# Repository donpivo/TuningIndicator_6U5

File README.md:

# TuningIndicator_6U5
Project description: https://retronics.no/2024/08/29/diy-digital-6u5-magic-eye-replacement/
All PCB design files (KiCAD), fabrication files (gerber), 3D models (.stl) and code (C++, PlatformIO) are shared for personal use only; not for commercial use / sale of neither the complete solution nor parts of it.

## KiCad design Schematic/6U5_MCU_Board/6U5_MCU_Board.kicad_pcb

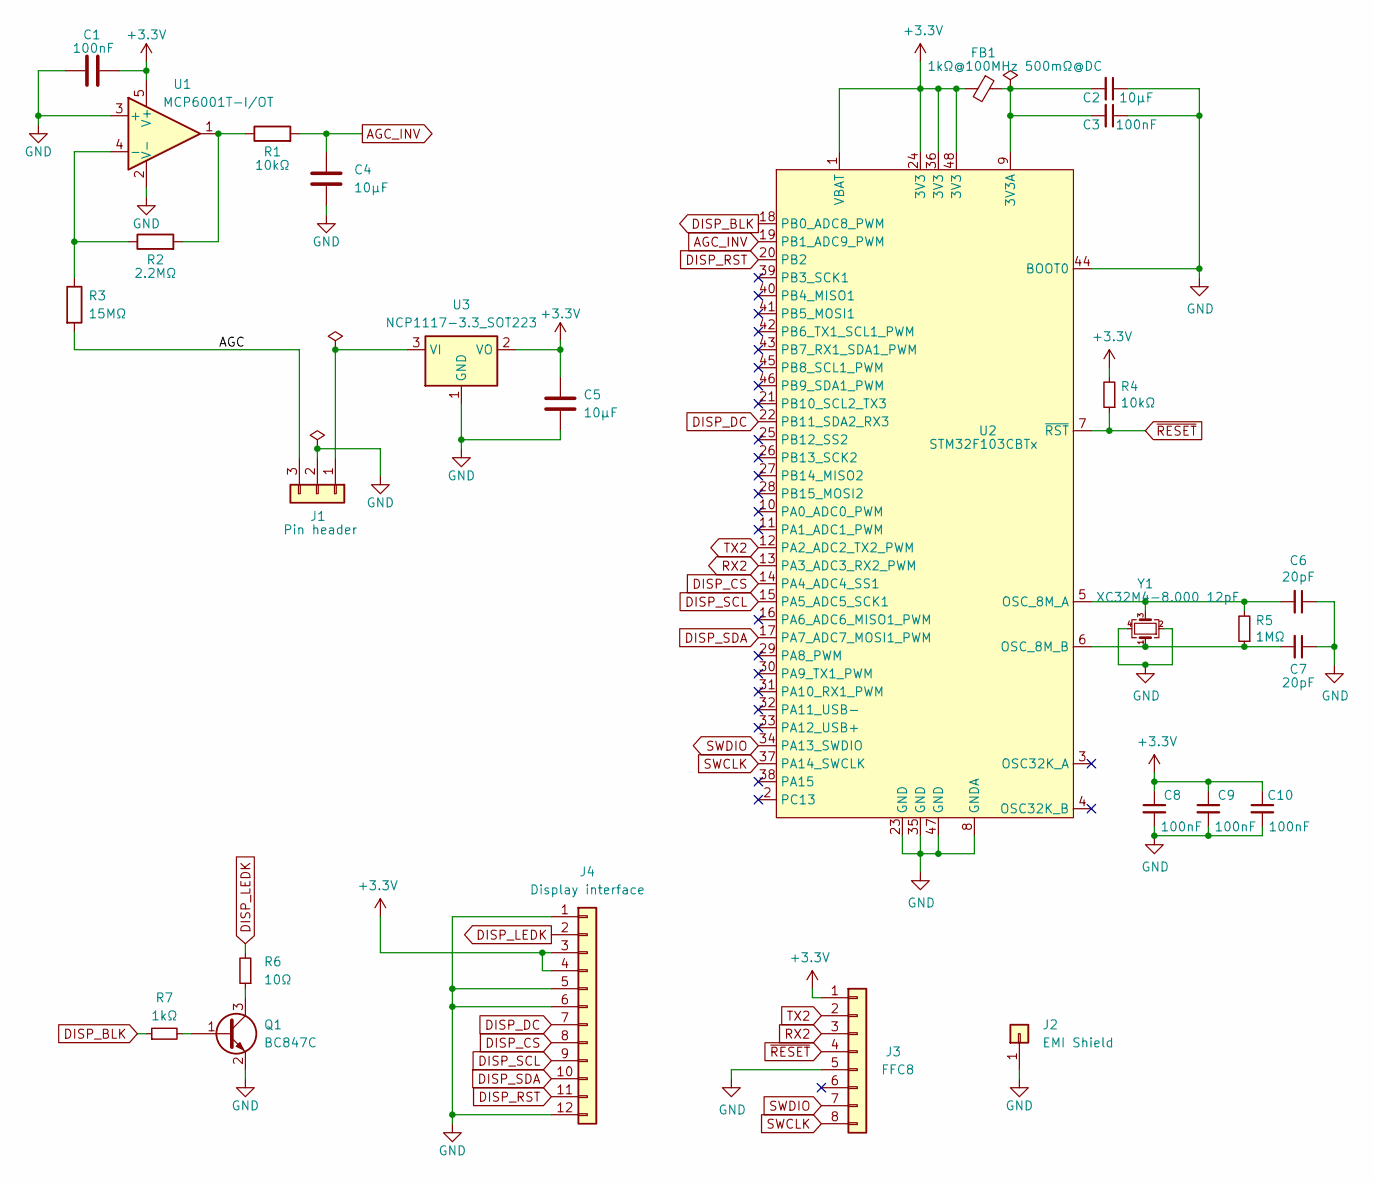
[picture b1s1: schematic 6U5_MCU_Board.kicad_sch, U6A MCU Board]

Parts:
C1, C3, C8, C9, C10: 100nF; C_0603_1608Metric_Pad1.08x0.95mm_HandSolder
C2, C4, C5: 10µF; C_0603_1608Metric_Pad1.08x0.95mm_HandSolder
C6, C7: 20pF; C_0603_1608Metric_Pad1.08x0.95mm_HandSolder
FB1: 1kΩ@100MHz 500mΩ@DC; L_0603_1608Metric_Pad1.05x0.95mm_HandSolder
J1: Pin header; PinHeader_1x03_P2.54mm_Horizontal_Alt
J2: EMI Shield; EMI_Shield_MS207-10S
J3: FFC8; 0527450897
J4: Display interface; 505110-1292
Q1: BC847C; SOT-23
R1, R4: 10kΩ; R_0603_1608Metric_Pad0.98x0.95mm_HandSolder
R2: 2.2MΩ; R_0603_1608Metric_Pad0.98x0.95mm_HandSolder
R3: 15MΩ; R_0603_1608Metric_Pad0.98x0.95mm_HandSolder
R5: 1MΩ; R_0603_1608Metric_Pad0.98x0.95mm_HandSolder
R6: 10Ω; R_0603_1608Metric_Pad0.98x0.95mm_HandSolder
R7: 1kΩ; R_0603_1608Metric_Pad0.98x0.95mm_HandSolder
U1: MCP6001T-I/OT; SOT-23-5
U2: STM32F103CBTx; LQFP-48_7x7mm_P0.5mm
U3: NCP1117-3.3_SOT223; SOT-223-3_TabPin2
Y1: XC32M4-8.000 12pF; Crystal_SMD_3225-4Pin_3.2x2.5mm

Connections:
+3.3V: C1.2, C5.1, C8.1, C9.1, C10.1, FB1.2, J3.1, J4.3, J4.4, R4.2, U1.5 (V+), U2.1 (VBAT), U2.24 (3V3), U2.36 (3V3), U2.48 (3V3), U3.2 (VO)
/AGC: J1.3, R3.2
AGC_INV: C4.1, R1.2, U2.19 (PB1_ADC9_PWM)
DISP_BLK: R7.1, U2.18 (PB0_ADC8_PWM)
DISP_CS: J4.8, U2.14 (PA4_ADC4_SS1)
DISP_DC: J4.7, U2.22 (PB11_SDA2_RX3)
DISP_LEDK: J4.2, R6.2
DISP_RST: J4.11, U2.20 (PB2)
DISP_SCL: J4.9, U2.15 (PA5_ADC5_SCK1)
DISP_SDA: J4.10, U2.17 (PA7_ADC7_MOSI1_PWM)
GND: C1.1, C2.1, C3.1, C4.2, C5.2, C6.1, C7.1, C8.2, C9.2, C10.2, J1.2, J2.1, J3.5, J4.1, J4.5, J4.6, J4.12, Q1.2 (E), U1.2 (V-), U1.3 (+), U2.8 (GNDA), U2.23 (GND), U2.35 (GND), U2.44 (BOOT0), U2.47 (GND), U3.1 (GND), Y1.2, Y1.4
unnamed: J1.1, U3.3 (VI)
unnamed: Q1.1 (B), R7.2
unnamed: Q1.3 (C), R6.1
unnamed: R1.1, R2.2, U1.1
unnamed: R2.1, R3.1, U1.4 (-)
unnamed: C2.2, C3.2, FB1.1, U2.9 (3V3A)
unnamed: C6.2, R5.2, U2.5 (OSC_8M_A), Y1.3
unnamed: C7.2, R5.1, U2.6 (OSC_8M_B), Y1.1
RX2: J3.3, U2.13 (PA3_ADC3_RX2_PWM)
SWCLK: J3.8, U2.37 (PA14_SWCLK)
SWDIO: J3.7, U2.34 (PA13_SWDIO)
TX2: J3.2, U2.12 (PA2_ADC2_TX2_PWM)
~RESET: J3.4, R4.1, U2.7 (~RST)

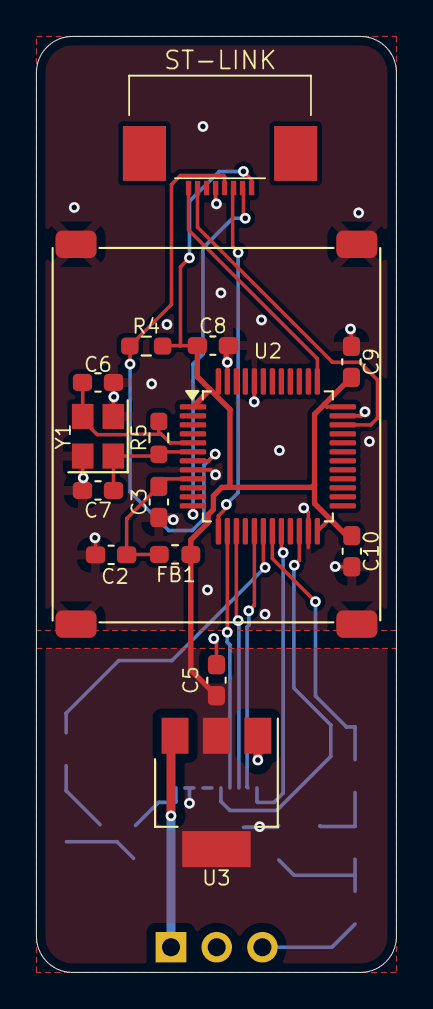
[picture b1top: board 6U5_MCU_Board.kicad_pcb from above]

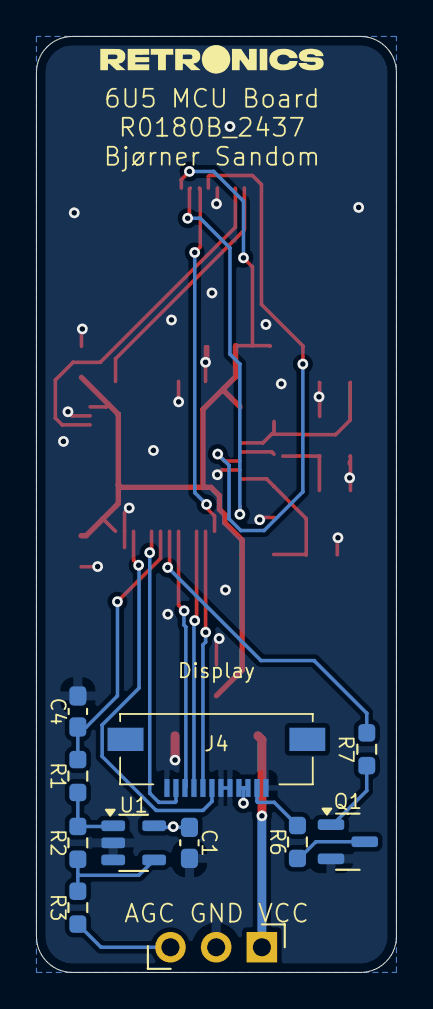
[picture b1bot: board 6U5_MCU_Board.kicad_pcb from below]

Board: 2 copper layers, 20.0 x 52.0 mm, 27 parts (11 on the bottom side), 24 nets.

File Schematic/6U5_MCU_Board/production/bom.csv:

Designator,Footprint,Quantity,Value,LCSC Part #
"C1, C10, C3, C8, C9",0603,5,100nF,
"C2, C4, C5",0603,3,10µF,
"C6, C7",0603,2,20pF,
FB1,0603,1,1kΩ@100MHz 500mΩ@DC,
J1,PinHeader_1x03_P2.54mm_Horizontal_Alt,1,Pin header,
J2,EMI_Shield_MS207-10S,1,EMI Shield,
J3,0527450897,1,FFC8,
J4,505110-1292,1,Display interface,
Q1,SOT-23,1,BC847C,
"R1, R4",0603,2,10kΩ,
R2,0603,1,2.2MΩ,
R3,0603,1,15MΩ,
R5,0603,1,1MΩ,
R6,0603,1,10Ω,
R7,0603,1,1kΩ,
U1,SOT-23-5,1,MCP6001T-I/OT,
U2,LQFP-48_7x7mm_P0.5mm,1,STM32F103CBTx,
U3,SOT-223-3_TabPin2,1,NCP1117-3.3_SOT223,
Y1,Crystal_SMD_3225-4Pin_3.2x2.5mm,1,XC32M4-8.000 12pF,

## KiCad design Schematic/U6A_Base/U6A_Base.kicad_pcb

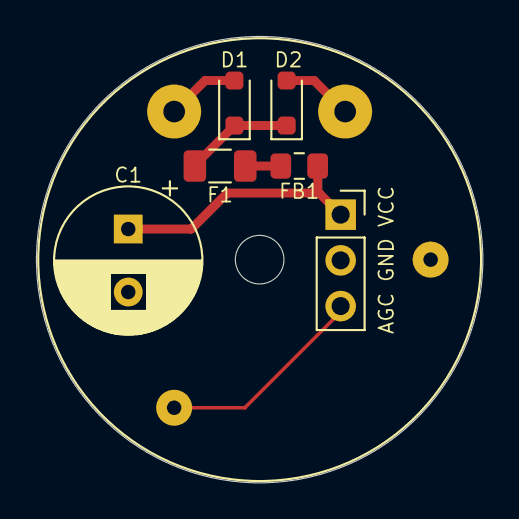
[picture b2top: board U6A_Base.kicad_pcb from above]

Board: 2 copper layers, 24.8 x 24.8 mm, 8 parts (0 on the bottom side), 7 nets.

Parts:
C1: 1000µF 16V; CP_Radial_D8.0mm_P3.50mm_H21mm
D1, D2: 1N5819WS; D_SOD-323_HandSoldering
F1: T1A; Fuse_1206_3216Metric
FB1: 330Ω@100MHz; L_0805_2012Metric_Pad1.15x1.40mm_HandSolder
H1: MountingHole; MountingHole_2.7mm_M2.5
J1: U6A Base; U6A_Base
J2: Pin header; PinSocket_1x03_P2.54mm_Vertical

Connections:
AGC: J1.3, J2.3
GND: C1.2, J1.5, J2.2
H1: D1.2 (A), J1.1
H2: D2.2 (A), J1.6
unnamed: D1.1 (K), D2.1 (K), F1.1
unnamed: F1.2, FB1.1
VCC: C1.1, FB1.2, J2.1

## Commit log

2024-08-29 Brightness and color adjustment
2024-08-29 Added display driver library reference
2024-08-29 File cleanup
2024-08-31 Removed unused code
2024-09-03 Re-attached EMI shield
2024-09-03 Added GFX library version
2024-09-14 Added thermal reliefs on bottom ground plane
